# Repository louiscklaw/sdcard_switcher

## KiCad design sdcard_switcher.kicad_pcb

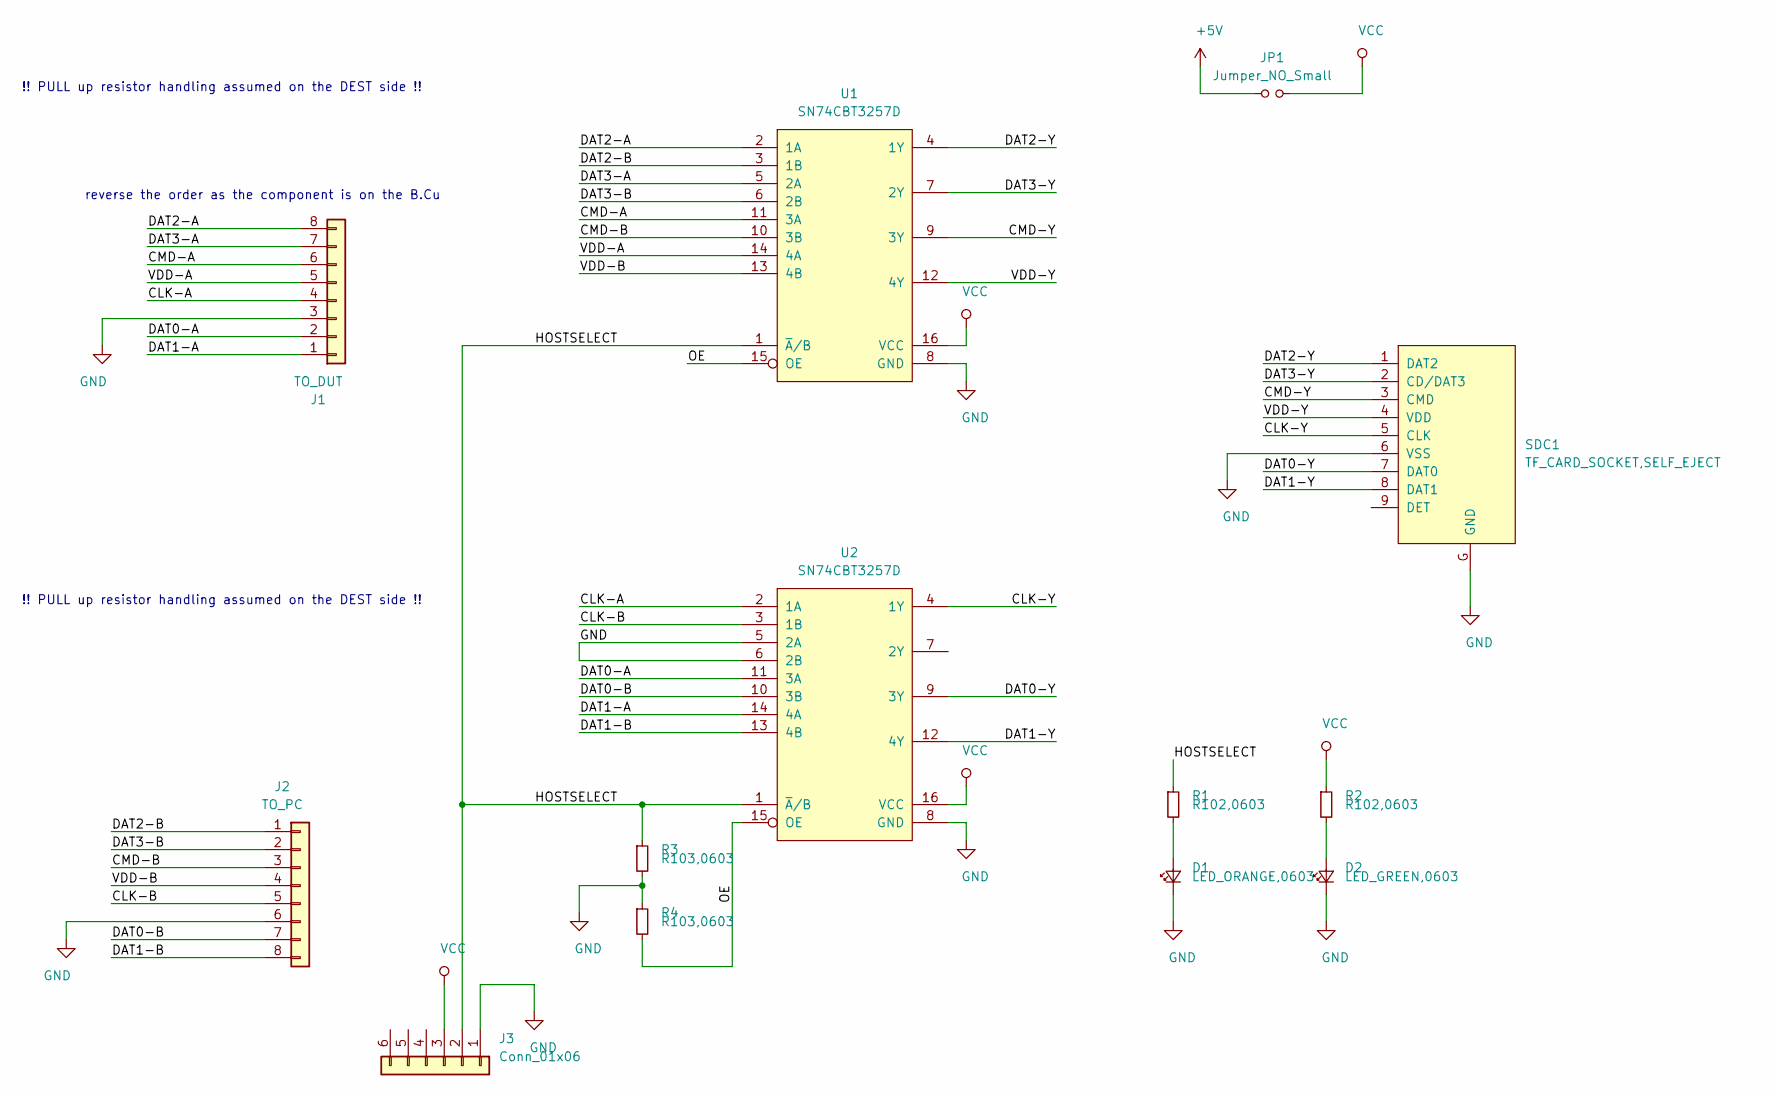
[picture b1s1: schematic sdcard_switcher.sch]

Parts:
D1: LED_ORANGE,0603; LED_0603_1608Metric_Pad1.05x0.95mm_HandSolder
D2: LED_GREEN,0603; LED_0603_1608Metric_Pad1.05x0.95mm_HandSolder
J1: TO_DUT; TE_84952-8_1x08-1MP_P1.0mm_Horizontal
J2: TO_PC; TE_84952-8_1x08-1MP_P1.0mm_Horizontal
J3: Conn_01x06; PinHeader_1x06_P1.27mm_Vertical
JP1: Jumper_NO_Small; SolderJumper-2_P1.3mm_Open_TrianglePad1.0x1.5mm
R1, R2: R102,0603; R_0603_1608Metric_Pad1.05x0.95mm_HandSolder
R3, R4: R103,0603; R_0603_1608Metric_Pad1.05x0.95mm_HandSolder
SDC1: TF_CARD_SOCKET,SELF_EJECT; SUNTECH_ST-TF-003A
U1, U2: SN74CBT3257D; TSSOP-16_4.4x5mm_P0.65mm

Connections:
+5V: JP1.1
/CLK-A: J1.4, U2.2 (1A)
/CLK-B: J2.5, U2.3 (1B)
/CLK-Y: SDC1.5 (CLK), U2.4 (1Y)
/CMD-A: J1.6, U1.11 (3A)
/CMD-B: J2.3, U1.10 (3B)
/CMD-Y: SDC1.3 (CMD), U1.9 (3Y)
/DAT0-A: J1.2, U2.11 (3A)
/DAT0-B: J2.7, U2.10 (3B)
/DAT0-Y: SDC1.7 (DAT0), U2.9 (3Y)
/DAT1-A: J1.1, U2.14 (4A)
/DAT1-B: J2.8, U2.13 (4B)
/DAT1-Y: SDC1.8 (DAT1), U2.12 (4Y)
/DAT2-A: J1.8, U1.2 (1A)
/DAT2-B: J2.1, U1.3 (1B)
/DAT2-Y: SDC1.1 (DAT2), U1.4 (1Y)
/DAT3-A: J1.7, U1.5 (2A)
/DAT3-B: J2.2, U1.6 (2B)
/DAT3-Y: SDC1.2 (CD/DAT3), U1.7 (2Y)
/HOSTSELECT: J3.2, R1.1, R3.1, U1.1 (~A~/B), U2.1 (~A~/B)
/OE: R4.2, U1.15 (OE), U2.15 (OE)
/VDD-A: J1.5, U1.14 (4A)
/VDD-B: J2.4, U1.13 (4B)
/VDD-Y: SDC1.4 (VDD), U1.12 (4Y)
GND: D1.1 (K), D2.1 (K), J1.3, J2.6, J3.1, R3.2, R4.1, SDC1.6 (VSS), SDC1.G (GND), U1.8 (GND), U2.5 (2A), U2.6 (2B), U2.8 (GND)
unnamed: D1.2 (A), R1.2
unnamed: D2.2 (A), R2.2
VCC: J3.3, JP1.2, R2.1, U1.16 (VCC), U2.16 (VCC)

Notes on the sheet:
!! PULL up resistor handling assumed on the DEST side !!
reverse the order as the component is on the B.Cu

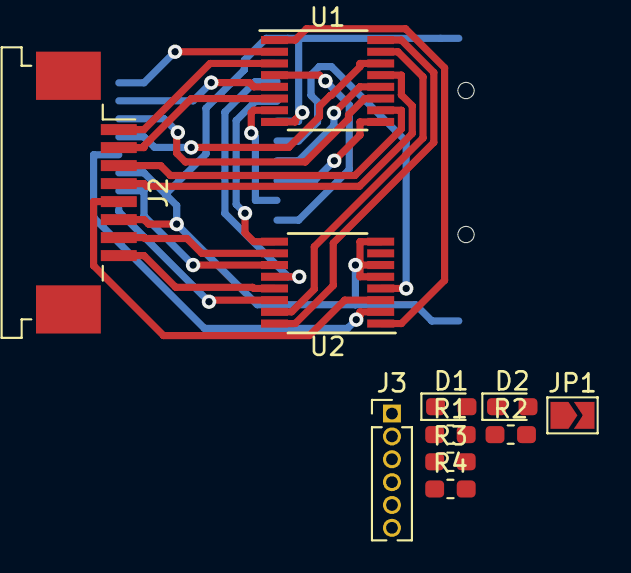
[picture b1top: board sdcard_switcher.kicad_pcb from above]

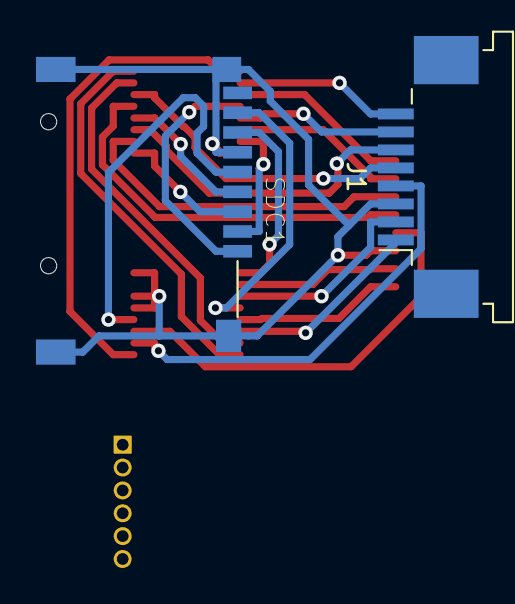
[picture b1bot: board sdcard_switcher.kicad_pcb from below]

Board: 2 copper layers, 13 parts (2 on the bottom side), 27 nets.

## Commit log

2018-12-14 update,
2020-05-05 ci: init travis build config,
2020-05-05 ci: init travis token,
